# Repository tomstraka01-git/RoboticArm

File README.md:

# Robotic Arm

Robotic arm is a  project about making my own robotic arm from scratch. I designed the arm from scratch and i plan to 3D print the file. Both firmware codes are written by me. The C++ code will run on  microcontroller, i will be using pico 2. The python code can be run on any computer wich can run python files. 

## Operation
First assemble the arm and try to set the servos in 90 degrees position. Then compile the code and wire everything together. After that run the python code and connnect the microcontroller via usb to your computer. Then use the python code to operate it, send signals, set position and record position. The main inverse and forward kinematics run on the pc, the c++ microcontroller code just recieves the serial commands. It uses cosine ease when animating through the listbox to make the movement seems smooth, moves nonlinearly.

### Keybinds
Use keybinds to control the robotic arm easily.
```
[t]: increments the time by 0.5 seconds
[q]: closes the serial port and GUI
[l]: loads animation
[s]: saves animation
[space]: animates smoothly through loaded positions or angles
[r]: records the current position onto the listbox
```

## What can it do?
You can set positions manually, record and play animations, pick up objects, use it to help you in your everyday life.

## Circuit
The circuit consists of a microcontroller, can be any but i chose pico 2. A PCA9685 servo driver servos, exteral power source and i pcb i will use from my other project. Connect servos to the pcb pins, and connect gnd to gnd and 5V to pcb 5V. Connect signal pins from pcb pins to PCA9685 signal pins. Connect sda scl and power pins from pico 2 to PCA9685. Then upload the code and turn on the power supply. The power supply should be able to handle around 5v 10 amps for safety. The pcb connects the microcontroller, has the adc voltage dividers, output pins for servos, etc. It connects everything together and makes it simplier. It also has some features i am not using like the fans or the adc, but are in the robotic dog project.

Here you can see how the pcb will fit into the assembly, the red lines indicate where it will be cut, to save space and remove features from another project i dont need.

## How to print?
If you want to replicate the project, you need to buy simillar servos, use some i2c pwm generation module and some circuit to distribute the power. For printing downooad the 3d print file, and use a 3d printer, that has over 400mm print surface. I want to use pla, because it is cheap and okay for my project. You can use other filaments if you want. For my printer, Prusa XL, the slicer says that it would take 22 hours to print and 300 grams to print. Use any microcontroller wich has i2c and serial communication, upload the code and connect it via usb to pc running the python file. Then it should work.

## Why?
Why would i want to build this arm? Because it is a great learning oppurtunity that can teach me many new things. It is also a challange for me, because it is one of my first big projects. I also need a small assistant to help me move things around my desk.

### Bill of Materials (BOM)

| Name | Purpose | Quantity | Total Cost (USD) | Link | Distributor |
|:---|:---|:---:|:---:|:---|:---|
| Servo 30 cm connector cable extension Male - Female | Cable extension for servo so i can connect it to power and microcontroller when the cable is not long enough to reach it. | 2 | $4.68 | [Link](https://rpishop.cz/servomotory/2878-servo-30-cm-propojka-samec-samice.html) | rpishop.cz |
| Raspberry Pico 2 WH | It is the brain of the robotic arm, will be used to control the servos and if it works compute angles using inverse kynematic for the servos. | 1 | $10.98 | [Link](https://rpishop.cz/590613/raspberry-pico-2-wh/) | rpishop.cz |
| Professional Lab - PLA+ Filament - black(1,75 mm, 1 kg) | It is the filment i will use to print the robotic arm fusion 360 model | 1 | $10.80 | [Link](https://rpishop.cz/616058/professional-lab-pla-plus-cerny/) | rpishop.cz |
| Servo motor MG996R 13 kg, 180° | Motors of the arm, will rotate the joints | 3 | $18.60 | [Link](https://rpishop.cz/641352/servo-mg996r-13-kg/) | rpishop.cz |
| **Total** | | | **$45.06** | | |

Note: PCA9685 I2C driver and power supply were reused from previous projects / already owned, $0 cost.

Made by Tomáš Straka for Statis Hackathon by hackclub.

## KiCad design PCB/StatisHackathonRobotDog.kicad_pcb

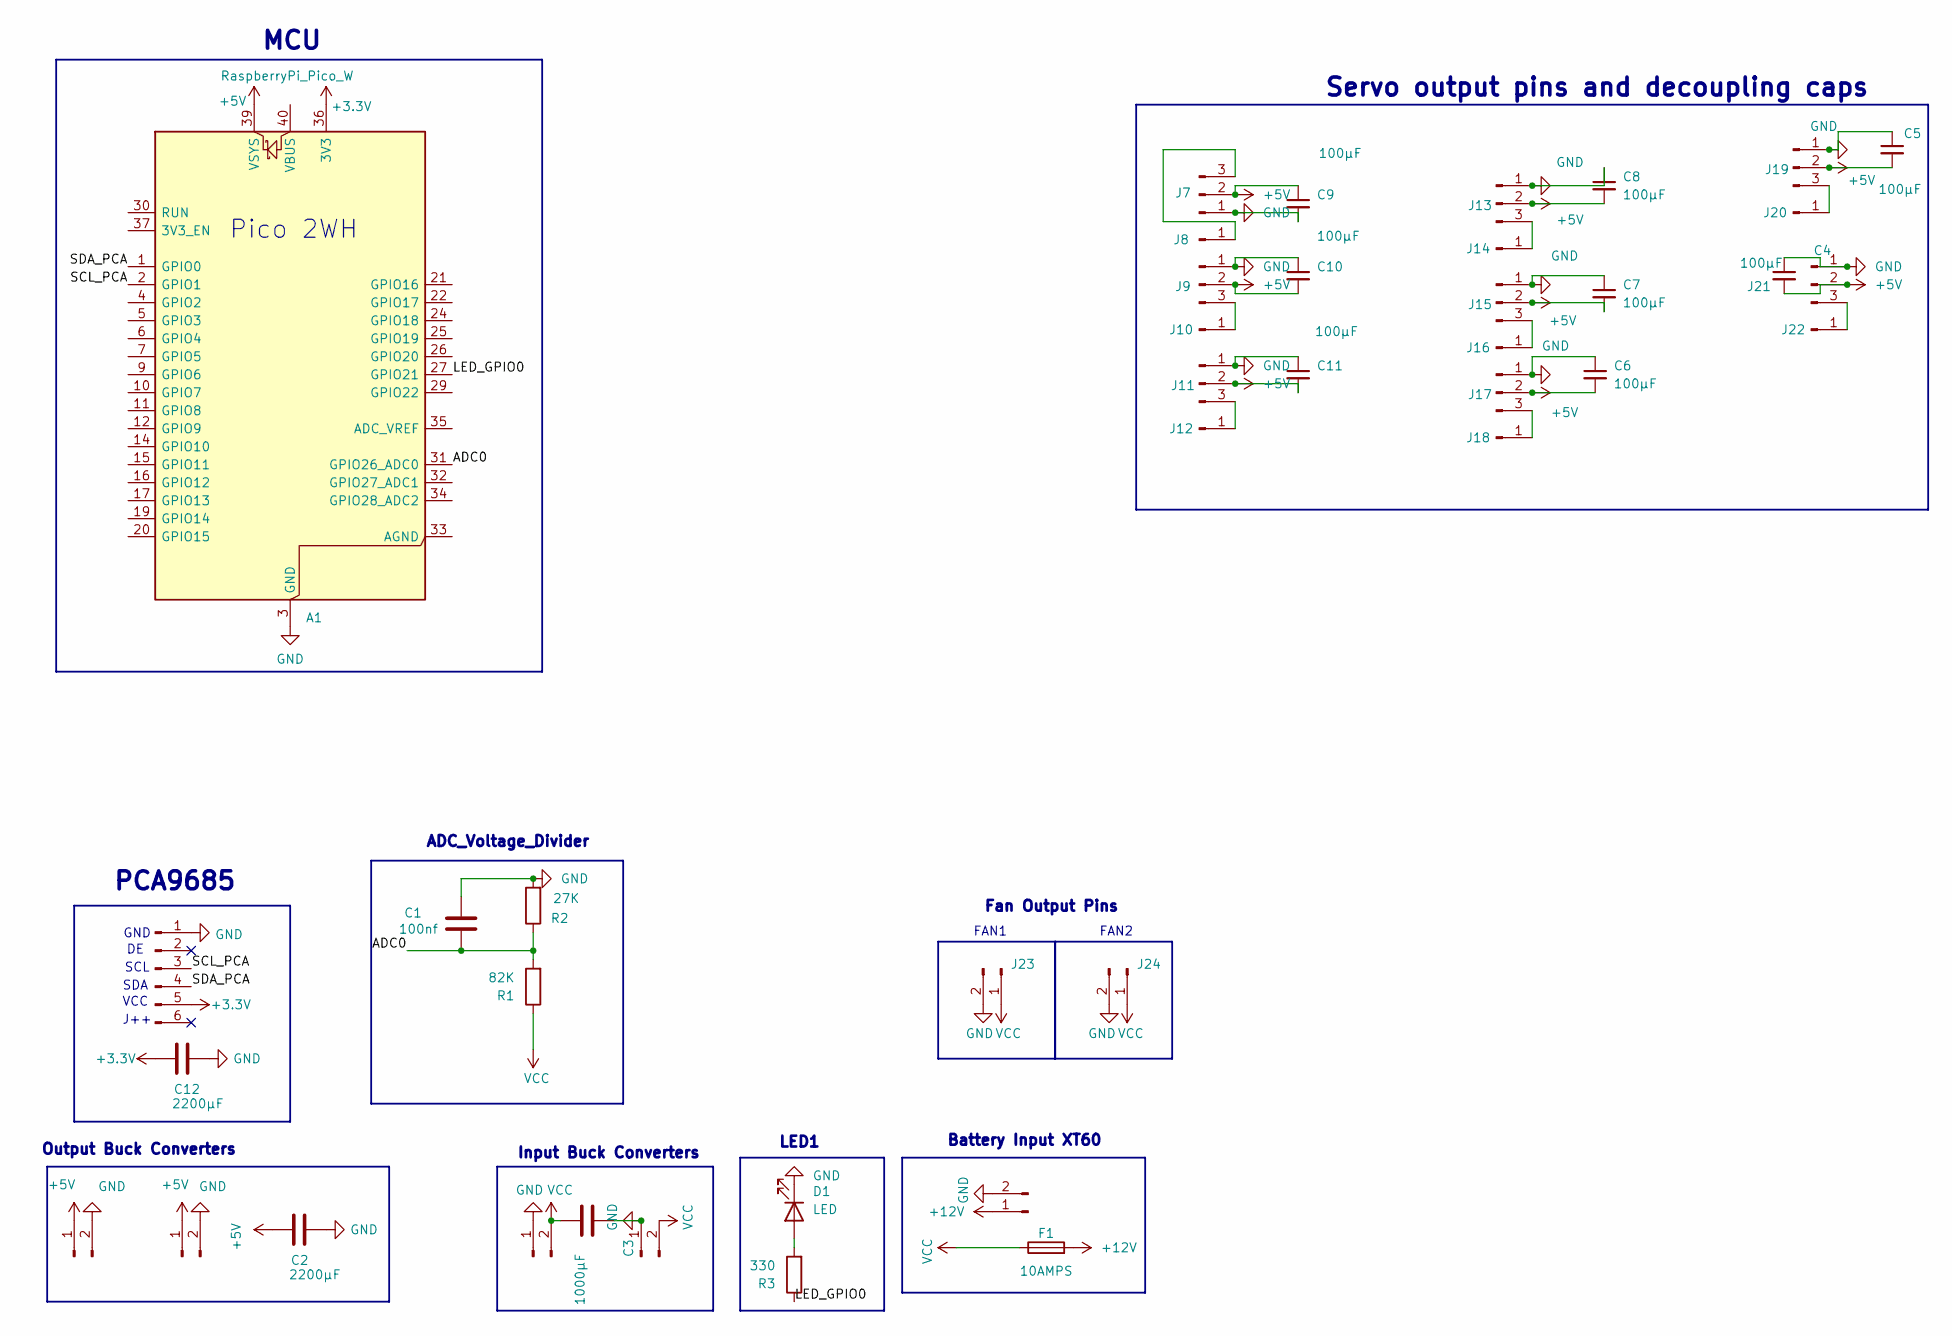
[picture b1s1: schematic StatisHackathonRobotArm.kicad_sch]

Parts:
A1: RaspberryPi_Pico_W; RaspberryPi_Pico_Common_THT
C1: 100nf; C_Disc_D5.0mm_W2.5mm_P5.00mm
C2, C12: 2200µF; C_Disc_D5.0mm_W2.5mm_P5.00mm
C3: 1000µF; C_Disc_D5.0mm_W2.5mm_P5.00mm
C4, C5, C6, C7, C8, C9, C10, C11: 100µF; C_1210_3225Metric_Pad1.33x2.70mm_HandSolder
D1: LED; LED_D5.0mm_Clear
F1: 10AMPS; Fuseholder_Littelfuse_445_030_series_5x20mm
J1: Conn_01x06_Pin; PinHeader_1x06_P2.54mm_Vertical
J2: Conn_01x02_Pin; AMASS_XT60-M_1x02_P7.20mm_Vertical
J3, J5, J6: Conn_01x02_Pin; TerminalBlock_Ningbo-Kagnex_HB9500M_1x02_P9.5mm
J4: Connector_PinHeader_2.54mm:PinHeader_1x02_P2.54mm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; TerminalBlock_Ningbo-Kagnex_HB9500M_1x02_P9.5mm
J7, J9, J11, J13, J15, J17, J19, J21: Conn_01x03_Pin; PinHeader_1x03_P2.54mm_Vertical
J8, J10, J12, J14, J16, J18, J20, J22: Conn_01x01_Pin; PinHeader_1x01_P2.54mm_Vertical
J23, J24: Conn_01x02_Pin; TerminalBlock_Phoenix_MKDS-1,5-2-5.08_1x02_P5.08mm_Horizont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
R1: 82K; R_Axial_DIN0207_L6.3mm_D2.5mm_P15.24mm_Horizontal
R2: 27K; R_Axial_DIN0207_L6.3mm_D2.5mm_P15.24mm_Horizontal
R3: 330; R_Axial_DIN0207_L6.3mm_D2.5mm_P15.24mm_Horizontal

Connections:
+3.3V: A1.36 (3V3), C12.2, J1.5
+5V: A1.39 (VSYS), C2.2, C4.2, C5.2, C6.2, C7.2, C8.2, C9.1, C10.2, C11.2, J4.1, J6.1, J7.2, J9.2, J11.2, J13.2, J15.2, J17.2, J19.2, J21.2
+12V: F1.2, J2.1
/ADC0: A1.31 (GPIO26_ADC0), C1.2, R1.2, R2.1
/LED_GPIO0: A1.27 (GPIO21), R3.1
/SCL_PCA: A1.2 (GPIO1), J1.3
/SDA_PCA: A1.1 (GPIO0), J1.4
GND: A1.3 (GND), A1.8 (GND), A1.13 (GND), A1.18 (GND), A1.23 (GND), A1.28 (GND), A1.38 (GND), C1.1, C2.1, C3.1, C4.1, C5.1, C6.1, C7.1, C8.1, C9.2, C10.1, C11.1, C12.1, D1.1 (K), J1.1, J2.2, J3.1, J4.2, J5.1, J6.2, J7.1, J9.1, J11.1, J13.1, J15.1, J17.1, J19.1, J21.1, J23.2, J24.2, R2.2
unnamed: D1.2 (A), R3.2
unnamed: J7.3, J8.1 (Pin_1_1)
unnamed: J9.3, J10.1 (Pin_1_1)
unnamed: J11.3, J12.1 (Pin_1_1)
unnamed: J13.3, J14.1 (Pin_1_1)
unnamed: J15.3, J16.1 (Pin_1_1)
unnamed: J17.3, J18.1 (Pin_1_1)
unnamed: J19.3, J20.1 (Pin_1_1)
unnamed: J21.3, J22.1 (Pin_1_1)
VCC: C3.2, F1.1, J3.2, J5.2, J23.1, J24.1, R1.1

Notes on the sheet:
GND
FAN2
Servo output pins and decoupling caps
J++
VCC
Output Buck Converters
Fan Output Pins
Input Buck Converters
SDA
PCA9685
MCU
Battery Input XT60
LED1
SCL
Pico 2WH
FAN1
ADC_Voltage_Divider

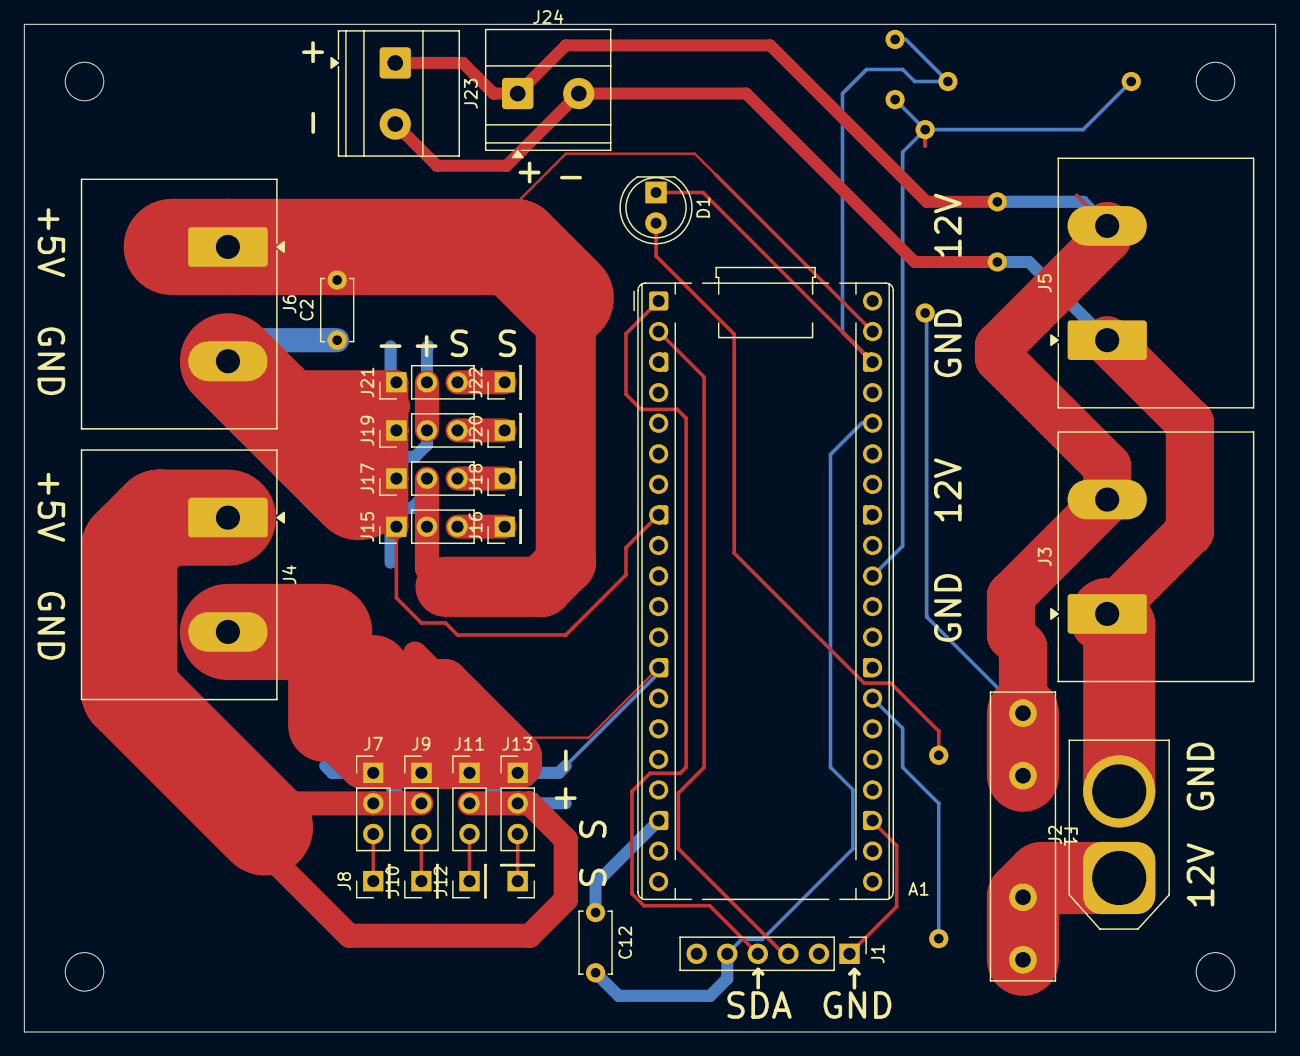
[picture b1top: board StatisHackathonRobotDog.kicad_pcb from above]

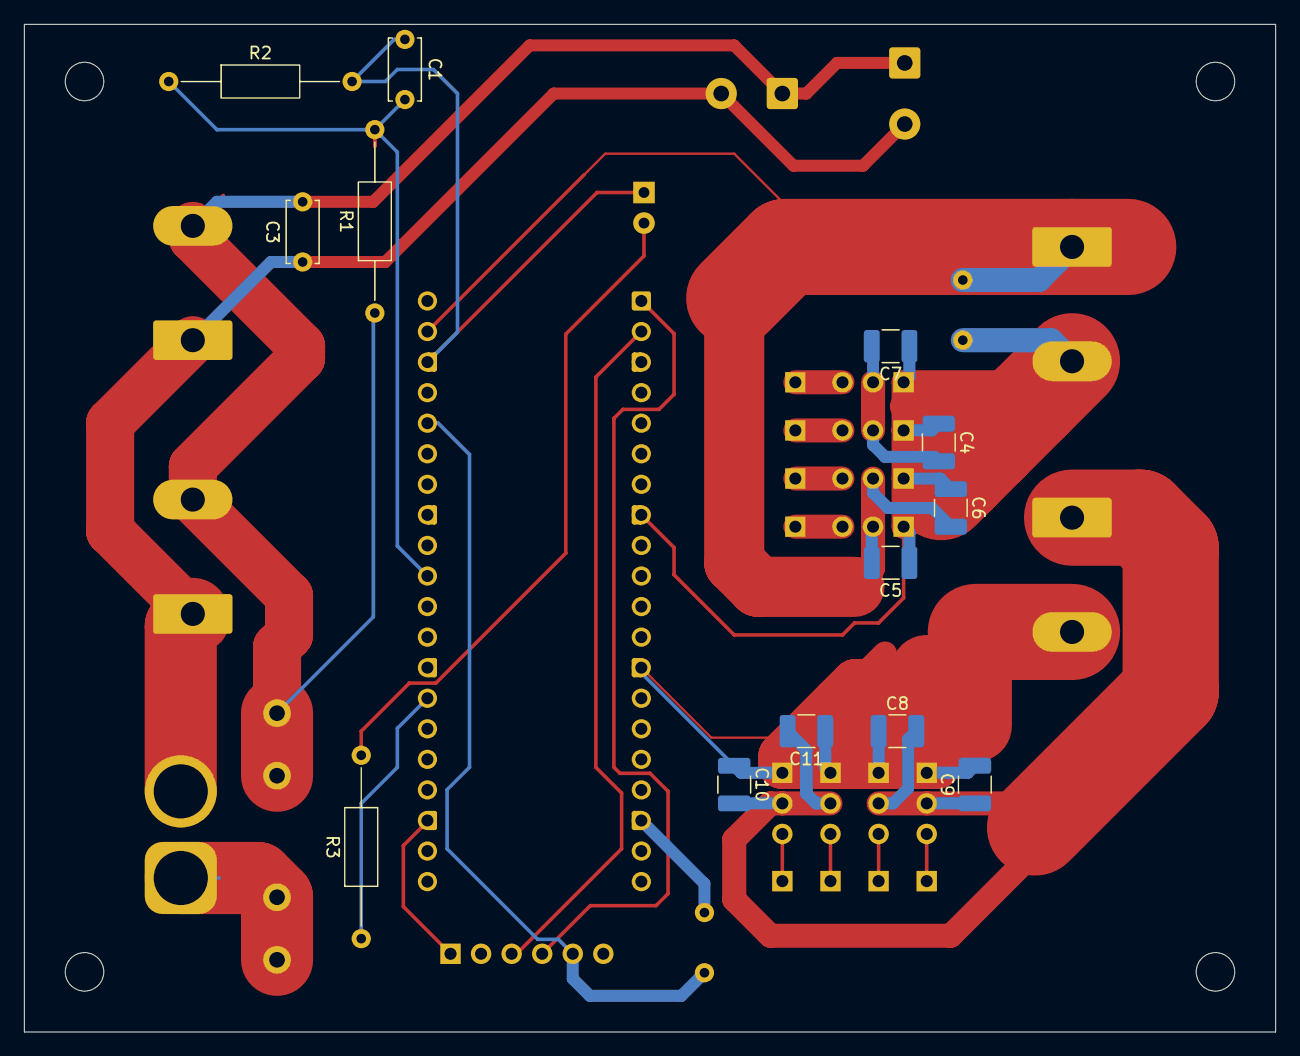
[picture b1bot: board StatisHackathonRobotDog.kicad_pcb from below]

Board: 2 copper layers, 104.0 x 83.8 mm, 42 parts (13 on the bottom side), 18 nets.

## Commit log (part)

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2026-04-09 Create test for image
2026-04-09 Project screenhots
2026-04-09 added screenshots
2026-04-09 fixed screenshot name
2026-04-12 first code commit
2026-04-16 changed the code added a lot of features
2026-04-17 added screenshot
2026-05-08 added 3d print file, changed code, tried migrating from microcontroller kinematics to pc ones, still not done
2026-05-08 fixed
2026-05-09 changed code and added fotos
2026-05-09 changed robotic arm code little
2026-05-10 added smoothing to code
2026-05-10 main code changes
2026-06-01 added photos, changed file names, added gerbers
2026-06-01 added 3d model of the pcb
2026-06-19 added pcb model to the main 3D model
